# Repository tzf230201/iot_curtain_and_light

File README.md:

# IoT Device for Curtain, Main Lighting, and RGB Ambient Light Control  

This project demonstrates an IoT device that controls a curtain motor, main lights, and an ambient light (which can also function as a sleep lamp). The device is powered by an ESP8266 microcontroller and integrates the Universal Telegram Bot library for remote control. The system offers four different modes of operation for flexible and convenient usage.

## Features

- **ESP8266-Based Control**: Enables wireless communication and control using the ESP8266 microcontroller.  
- **Telegram Bot Integration**: Allows real-time remote control via a dedicated Telegram bot.  
- **Four Operation Modes**:  
  1. **Button Control**: Manually control the curtain motor, room lighting, and RGB ambient light using physical buttons.  
  2. **LDR (Light Dependent Resistor) Control**: Automatically adjusts the lighting system based on ambient light levels.  
  3. **Time-Based Control**: Automates curtain and light operations using a Real-Time Clock (RTC) module.  
  4. **Direct Telegram Control**: Provides instant control through commands sent via Telegram.  

## Device Images  

- **Real Hardware**  
  
*Figure 1: Physical Board*

- **Board Design**  
  
*Figure 2: 3D Board Design*  

## Hardware Specifications  

*Figure 3: Electronics Diagram*  

## Usage  

*Figure 4: Device in Action*  

1. **Physical Button Control**: Simply press the physical buttons to manage the curtain motor, room lights, and RGB ambient light.  
2. **Automatic Mode**: The system automatically adjusts the main and ambient lighting based on the surrounding light detected by the LDR sensor.  
3. **Time-Based Mode**: Set schedules for automated curtain and light management.  
4. **Telegram Control**: Send specific commands through Telegram to remotely operate the curtain, room lighting, and ambient light.  

All control methods can be configured through the Telegram bot by sending the `/start` command.

Ask me anything : teukuzikrifatahillah@gmail.com

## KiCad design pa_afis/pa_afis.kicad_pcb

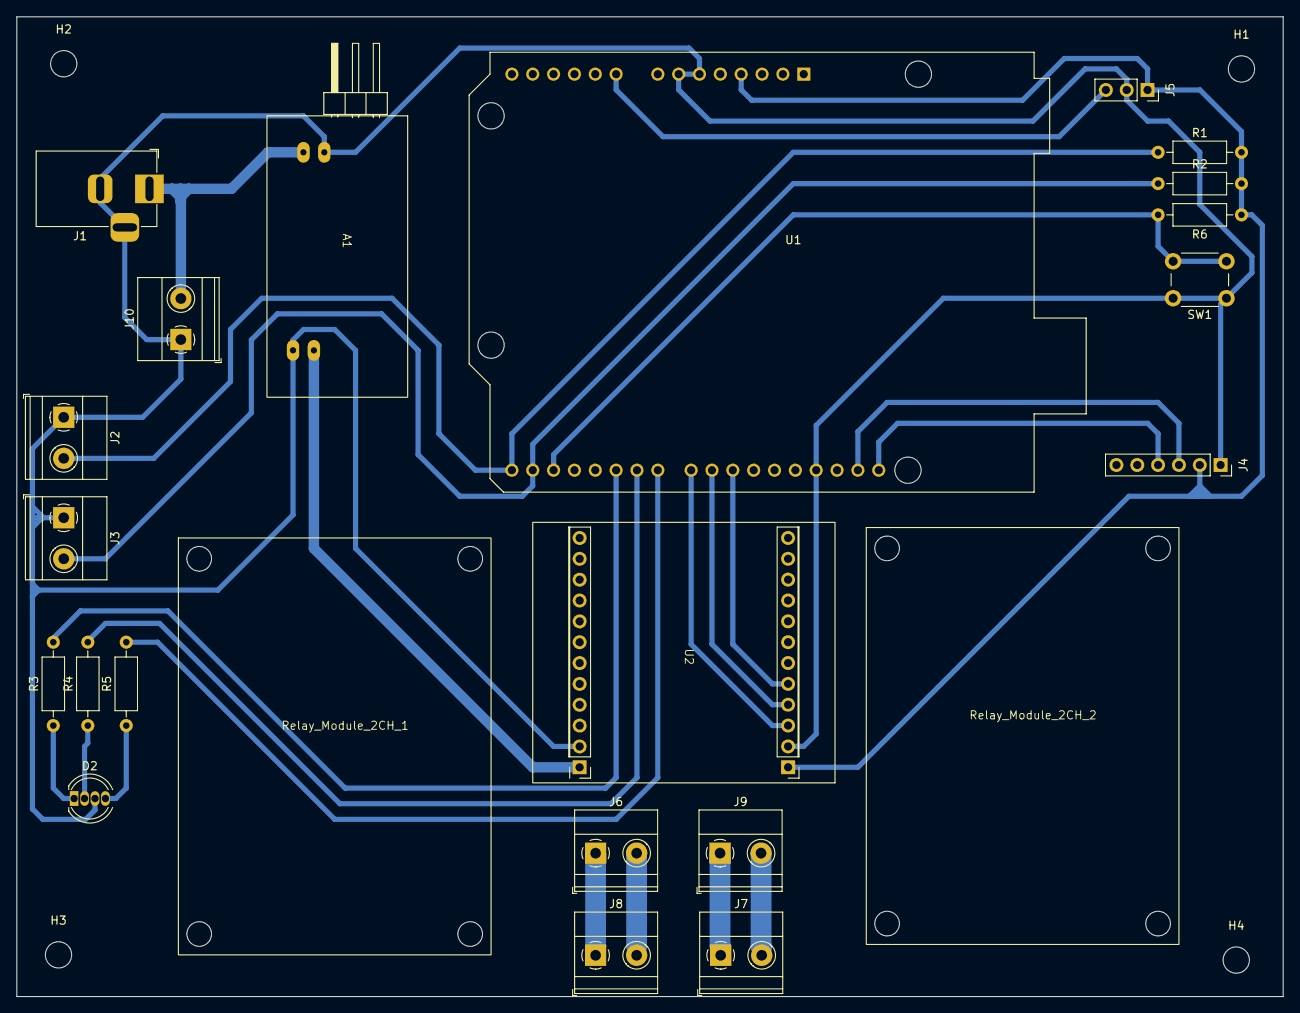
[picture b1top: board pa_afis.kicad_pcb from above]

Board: 2 copper layers, 154.3 x 119.4 mm, 27 parts (0 on the bottom side), 23 nets.

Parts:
A1: UBEC_Regulator; UBEC_Reg
D2: LED_RGKB; LED_D5.0mm-4_RGB
H1, H2, H3, H4: MountingHole; MountingHole_3.2mm_M3
J1: Barrel_Jack_Switch; BarrelJack_Horizontal
J2, J3, J6, J7, J8, J9, J10: Screw_Terminal_01x02; TerminalBlock_Phoenix_MKDS-1,5-2_1x02_P5.00mm_Horizontal
J4: Conn_01x06; PinSocket_1x06_P2.54mm_Vertical
J5: Conn_01x03; PinSocket_1x03_P2.54mm_Vertical
R1, R2, R3, R4, R5, R6: R; R_Axial_DIN0207_L6.3mm_D2.5mm_P10.16mm_Horizontal
Relay_Module_2CH_1, Relay_Module_2CH_2: Relay_Module_2CH
SW1: SW_Omron_B3FS; SW_PUSH_6mm
U1: Wemos_D1_R2; wemos_d1_r2
U2: level_converter

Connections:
+3.3V: J4.2, J5.1, R1.2, R2.2, R6.1, U1.4 (3V3), U2.1 (VCCA)
+5V: A1.4 (5v), U2.24 (VCCB)
+12V: A1.2 (VIN), J1.1, J10.2
A0: J5.3, U1.9 (A0)
D0: R6.2, SW1.2, U1.17 (~WAKE/D0)
D3: R3.2, U1.20 (D3)
D4: R4.2, U1.21 (D4)
D5: R5.2, U1.22 (D5)
D6: U1.23 (D6), U2.3 (A0)
D7: U1.24 (D7), U2.4 (A1)
D8: U1.25 (SS/D8), U2.5 (A2)
GND: A1.1 (GND), A1.3 (GND), D2.3 (K), J1.2, J1.3, J2.1, J3.1, J4.1, J5.2, J10.1, SW1.1, U1.6 (GND), U1.7 (GND), U1.29 (GND), U2.2 (GND), U2.23 (GND)
unnamed: D2.4 (BA), R5.1
unnamed: D2.2 (GA), R4.1
unnamed: D2.1 (RA), R3.1
unnamed: J2.2, R1.1, U1.15 (RX)
unnamed: J3.2, R2.1, U1.16 (TX)
unnamed: J6.1, J8.1
unnamed: J6.2, J8.2
unnamed: J7.1, J9.1
unnamed: J7.2, J9.2
SCL: J4.4, U1.32 (SCL/D1)
SDA: J4.3, U1.31 (SDA/D2)

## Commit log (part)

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2023-07-13 add files
2024-07-21 update documentation
